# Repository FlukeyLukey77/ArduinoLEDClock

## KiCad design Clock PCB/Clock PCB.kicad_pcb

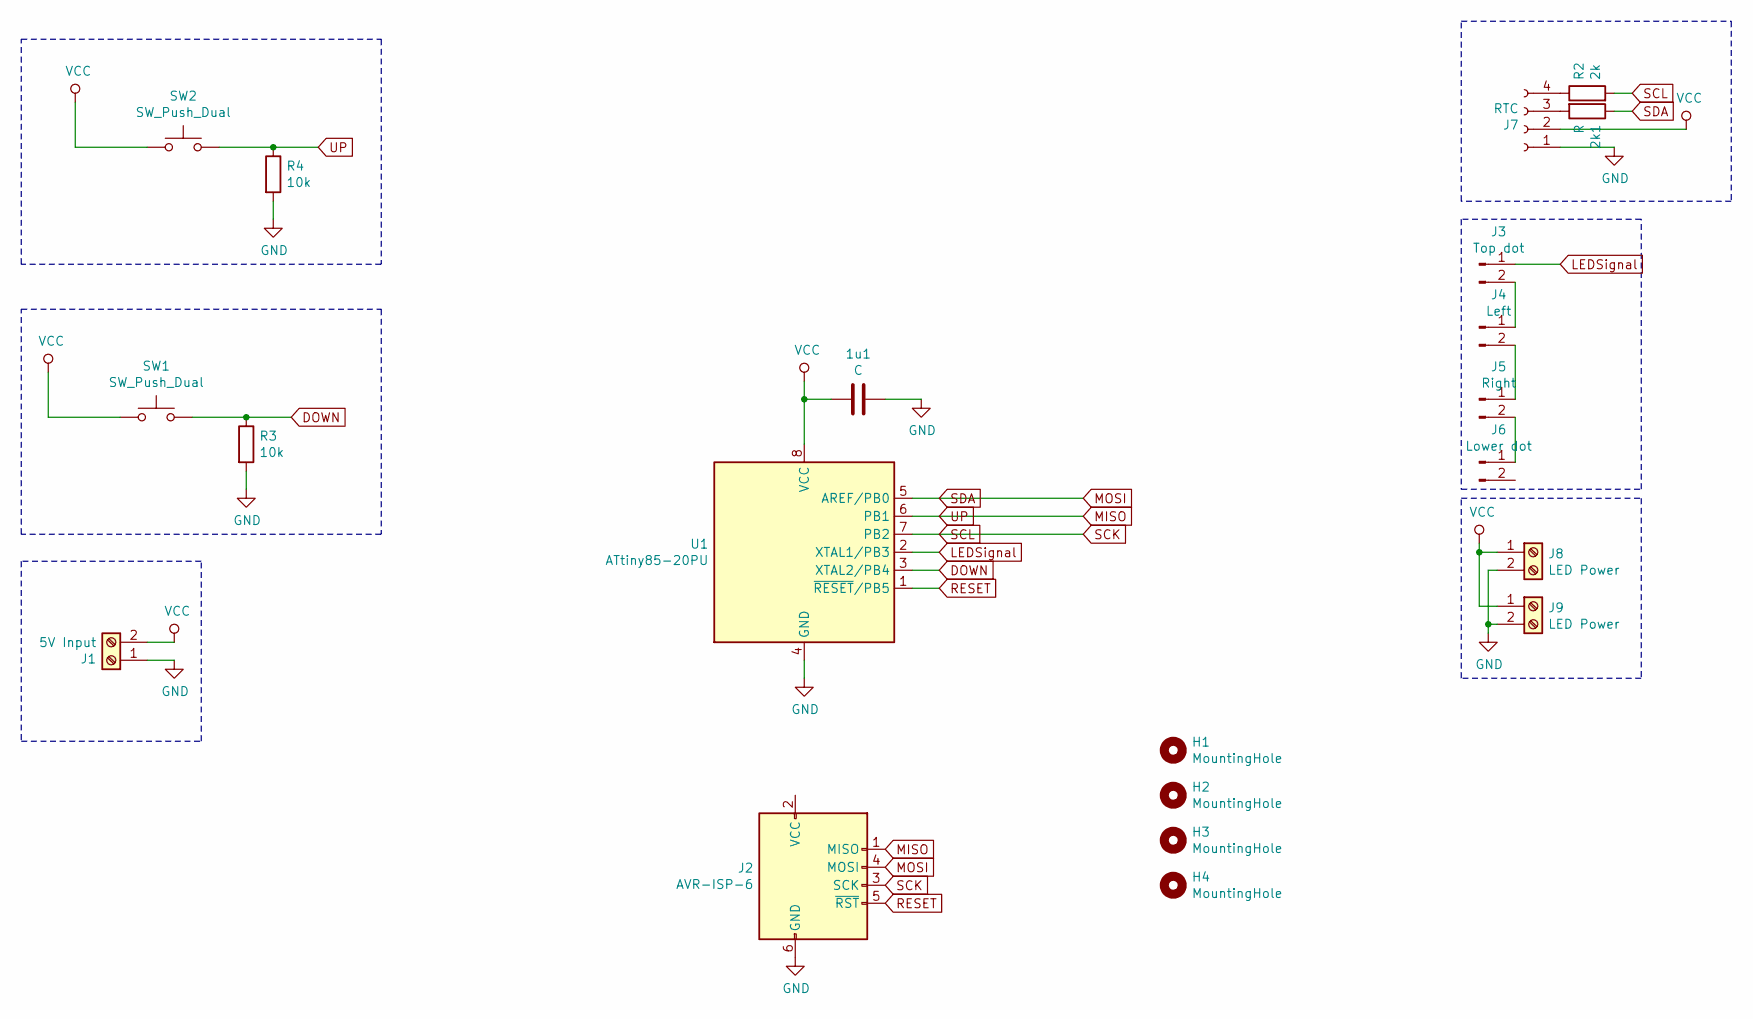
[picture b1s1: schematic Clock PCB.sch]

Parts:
1u1: C; C_Disc_D6.0mm_W2.5mm_P5.00mm
2k1: R; R_Axial_DIN0207_L6.3mm_D2.5mm_P7.62mm_Horizontal
H1, H2, H3, H4: MountingHole; MountingHole_3.2mm_M3
J1: 5V Input; TerminalBlock_bornier-2_P5.08mm
J2: AVR-ISP-6; PinHeader_2x03_P2.54mm_Vertical
J3: Top dot; PinHeader_1x02_P2.54mm_Horizontal
J4: Left; PinHeader_1x02_P2.54mm_Horizontal
J5: Right; PinHeader_1x02_P2.54mm_Horizontal
J6: Lower dot; PinHeader_1x02_P2.54mm_Vertical
J7: RTC; PinHeader_1x04_P2.54mm_Vertical
J8, J9: LED Power; TerminalBlock_bornier-2_P5.08mm
R2: 2k; R_Axial_DIN0207_L6.3mm_D2.5mm_P7.62mm_Horizontal
R3, R4: 10k; R_Axial_DIN0207_L6.3mm_D2.5mm_P7.62mm_Horizontal
SW1, SW2: SW_Push_Dual; SW_PUSH_6mm_H4.3mm
U1: ATtiny85-20PU; DIP-8_W7.62mm

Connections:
DOWN: R3.1, SW1.2, U1.3 (XTAL2/PB4)
GND: 1u1.1, J1.1, J2.6 (GND), J7.1, J8.2, J9.2, R3.2, R4.2, U1.4 (GND)
LEDSignal: J3.1, U1.2 (XTAL1/PB3)
MISO: J2.1 (MISO), R4.1, SW2.2, U1.6 (PB1)
MOSI: 2k1.1, J2.4 (MOSI), U1.5 (AREF/PB0)
unnamed: 2k1.2, J7.3
unnamed: J3.2, J4.1
unnamed: J4.2, J5.1
unnamed: J5.2, J6.1
unnamed: J7.4, R2.1
RESET: J2.5 (~RST), U1.1 (~RESET~/PB5)
SCK: J2.3 (SCK), R2.2, U1.7 (PB2)
VCC: 1u1.2, J1.2, J7.2, J8.1, J9.1, SW1.1, SW2.1, U1.8 (VCC)

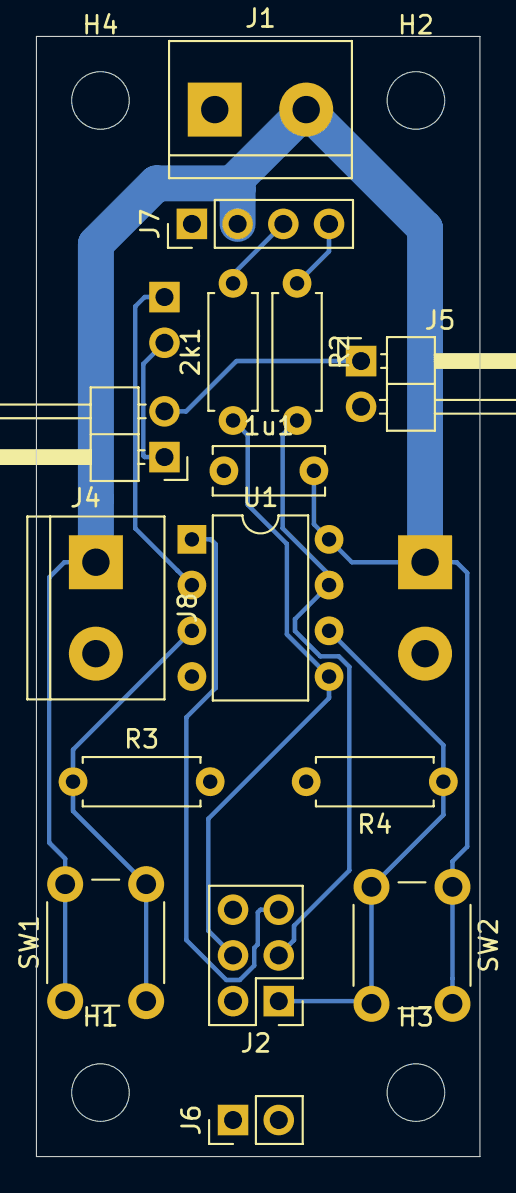
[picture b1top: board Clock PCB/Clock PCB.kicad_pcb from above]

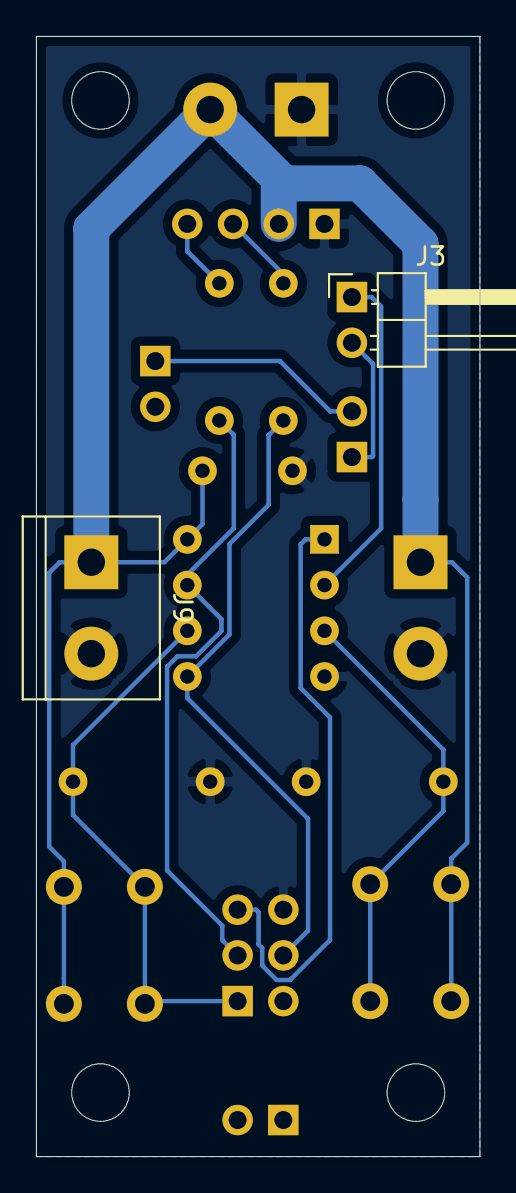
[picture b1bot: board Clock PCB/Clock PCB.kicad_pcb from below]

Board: 2 copper layers, 24.6 x 62.2 mm, 21 parts (2 on the bottom side), 13 nets.

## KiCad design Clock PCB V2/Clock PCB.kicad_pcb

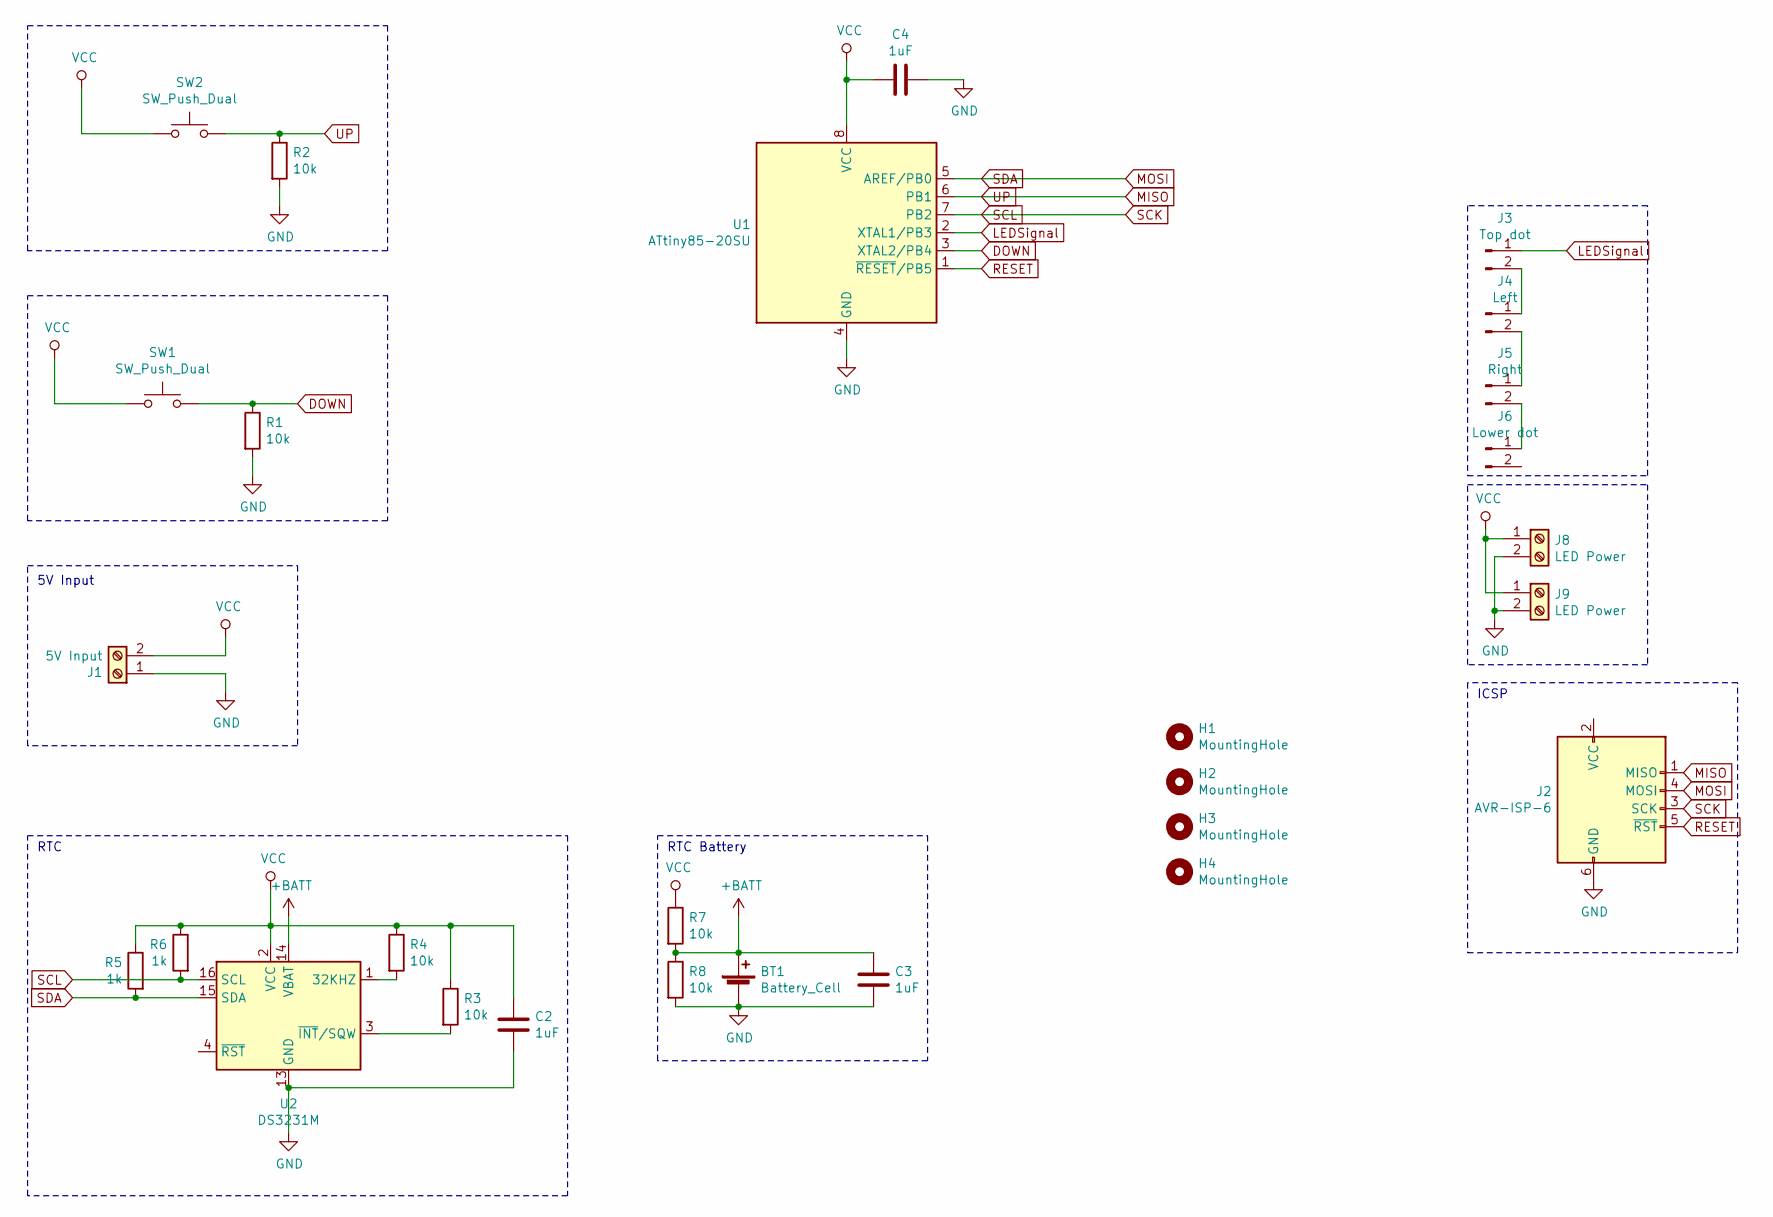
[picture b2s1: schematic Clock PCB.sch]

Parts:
BT1: Battery_Cell; PinHeader_1x02_P2.54mm_Horizontal
C2, C3, C4: 1uF; C_0805_2012Metric
H1, H2, H3, H4: MountingHole; MountingHole_3.2mm_M3
J1: 5V Input; TerminalBlock_bornier-2_P5.08mm
J2: AVR-ISP-6; PinHeader_2x03_P2.54mm_Vertical
J3: Top dot; PinHeader_1x02_P2.54mm_Horizontal
J4: Left; PinHeader_1x02_P2.54mm_Horizontal
J5: Right; PinHeader_1x02_P2.54mm_Horizontal
J6: Lower dot; PinHeader_1x02_P2.54mm_Horizontal
J8, J9: LED Power; TerminalBlock_bornier-2_P5.08mm
R1, R2, R3, R4, R7, R8: 10k; R_0805_2012Metric
R5, R6: 1k; R_0805_2012Metric
SW1, SW2: SW_Push_Dual; SW_PUSH_6mm_H4.3mm
U1: ATtiny85-20SU; SOIC-8_3.9x4.9mm_P1.27mm
U2: DS3231M; SOIC-16W_7.5x10.3mm_P1.27mm

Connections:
+BATT: BT1.1 (+), C3.1, R7.2, R8.1, U2.14 (VBAT)
DOWN: R1.1, SW1.2, U1.3 (XTAL2/PB4)
GND: BT1.2 (-), C2.2, C3.2, C4.1, J1.1, J2.6 (GND), J8.2, J9.2, R1.2, R2.2, R8.2, U1.4 (GND), U2.5 (GND), U2.6 (GND), U2.7 (GND), U2.8 (GND), U2.9 (GND), U2.10 (GND), U2.11 (GND), U2.12 (GND), U2.13 (GND)
LEDSignal: J3.1, U1.2 (XTAL1/PB3)
MISO: J2.1 (MISO), R2.1, SW2.2, U1.6 (PB1)
MOSI: J2.4 (MOSI), R5.2, U1.5 (AREF/PB0), U2.15 (SDA)
unnamed: J3.2, J4.1
unnamed: J4.2, J5.1
unnamed: J5.2, J6.1
unnamed: R3.2, U2.3 (~INT~/SQW)
unnamed: R4.2, U2.1 (32KHZ)
RESET: J2.5 (~RST), U1.1 (~RESET~/PB5)
SCK: J2.3 (SCK), R6.2, U1.7 (PB2), U2.16 (SCL)
VCC: C2.1, C4.2, J1.2, J8.1, J9.1, R3.1, R4.1, R5.1, R6.1, R7.1, SW1.1, SW2.1, U1.8 (VCC), U2.2 (VCC)

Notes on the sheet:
RTC
5V Input
ICSP
RTC Battery

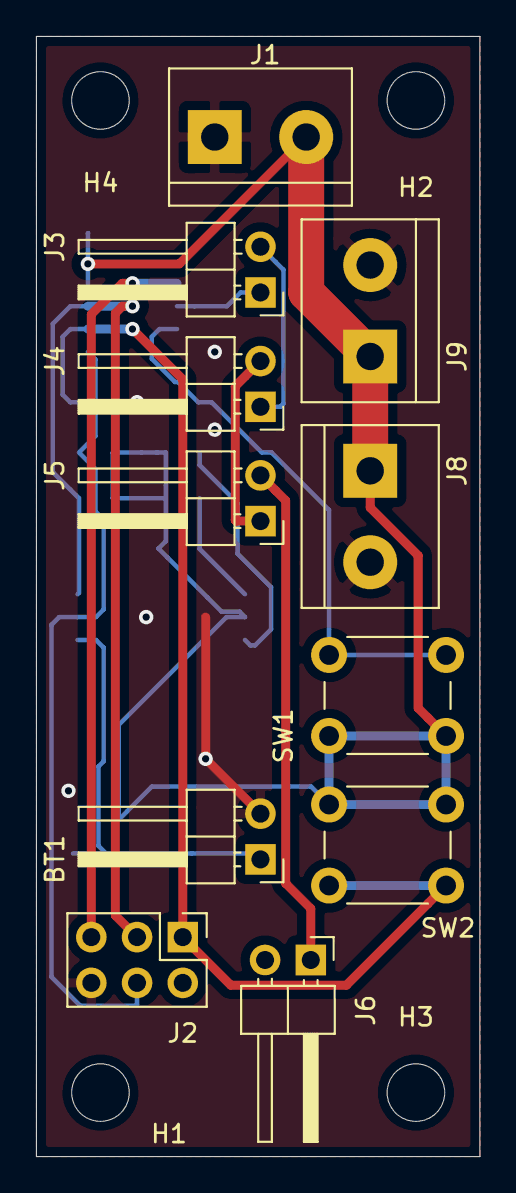
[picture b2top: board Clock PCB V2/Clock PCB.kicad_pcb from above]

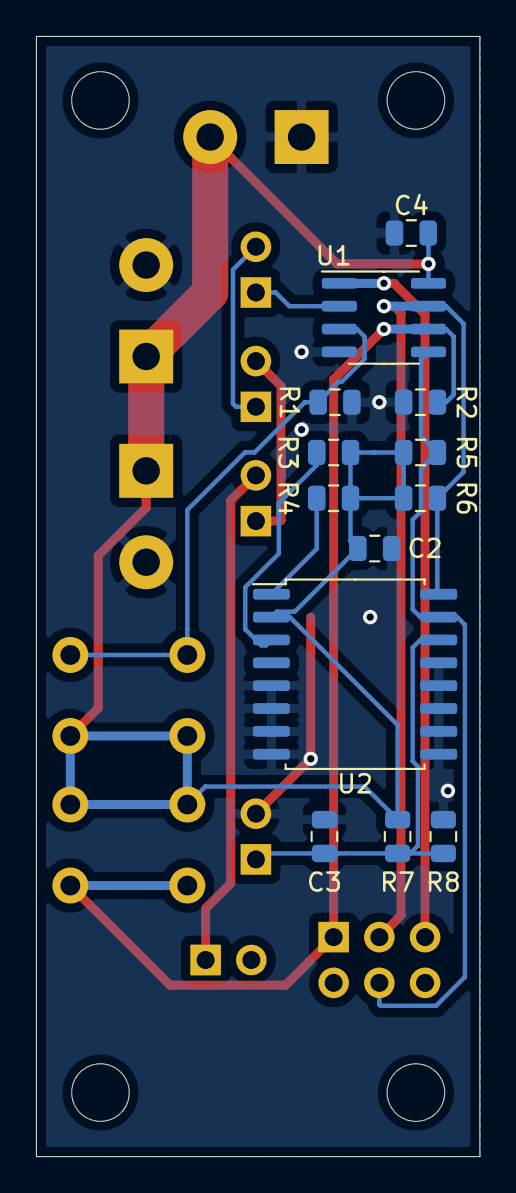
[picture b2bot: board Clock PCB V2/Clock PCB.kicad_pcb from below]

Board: 2 copper layers, 24.6 x 62.2 mm, 28 parts (13 on the bottom side), 14 nets.
